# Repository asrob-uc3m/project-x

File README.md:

# project-x
Carreras de coches RC en FPV

## Materiales

### Coche
* [Coche RC - Gearbest](https://www.gearbest.com/rc-cars/pp_614987.html?wid=1433363)

### Control & FPV
* [Gafas FPV - JMT EV800 - xt-xinte](https://www.xt-xinte.com/JMT-EV800-5-Inch-800x480-Detachable-Wearing-Glasses-FPV-Goggles-40CH-Raceband-For-FPV-Racer-Quadcopter-Drone-p553991.html)
* [Cámara FPV - xt-xinte](https://www.xt-xinte.com/FPV-AIO-Micro-Camera-5-8G-25MW-40CH-800TVL-Transmitter-LST-S2-FPV-Camera-w-OSD-p497464.html)

## Otros materiales posibles
No están siendo usados por el prototipo oficial, pero sí por otros prototipos:

* [Gafas FPV - Eachine VR-007 Pro - Banggood](https://www.banggood.com/Eachine-VR-007-Pro-VR007-5_8G-40CH-HD-FPV-Goggles-4_3-Inch-Video-Headset-With-3_7V-1600mAh-Battery-p-1134154.html?rmmds=search&cur_warehouse=USA)

## Atribuciones

* [Fuente logo](https://www.dafont.com/es/dream-mma.font?text=PROJECT-X&back=theme)

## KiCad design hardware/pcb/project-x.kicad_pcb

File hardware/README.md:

Hardware
----

* GERBER - Contiene los archivos GERBER para la fabricación de la PCB
* STL - Contiene los archivos STL para la fabricación de las piezas impresas
* pcb - Contiene los archivos fuente de la PCB del coche
* backpack.fcstd - La forma de la PCB del coche en un archivo CAD (para impresión 3D y pruebas)
* cam_holder.fcstd - Pieza para sujetar la cámara FPV

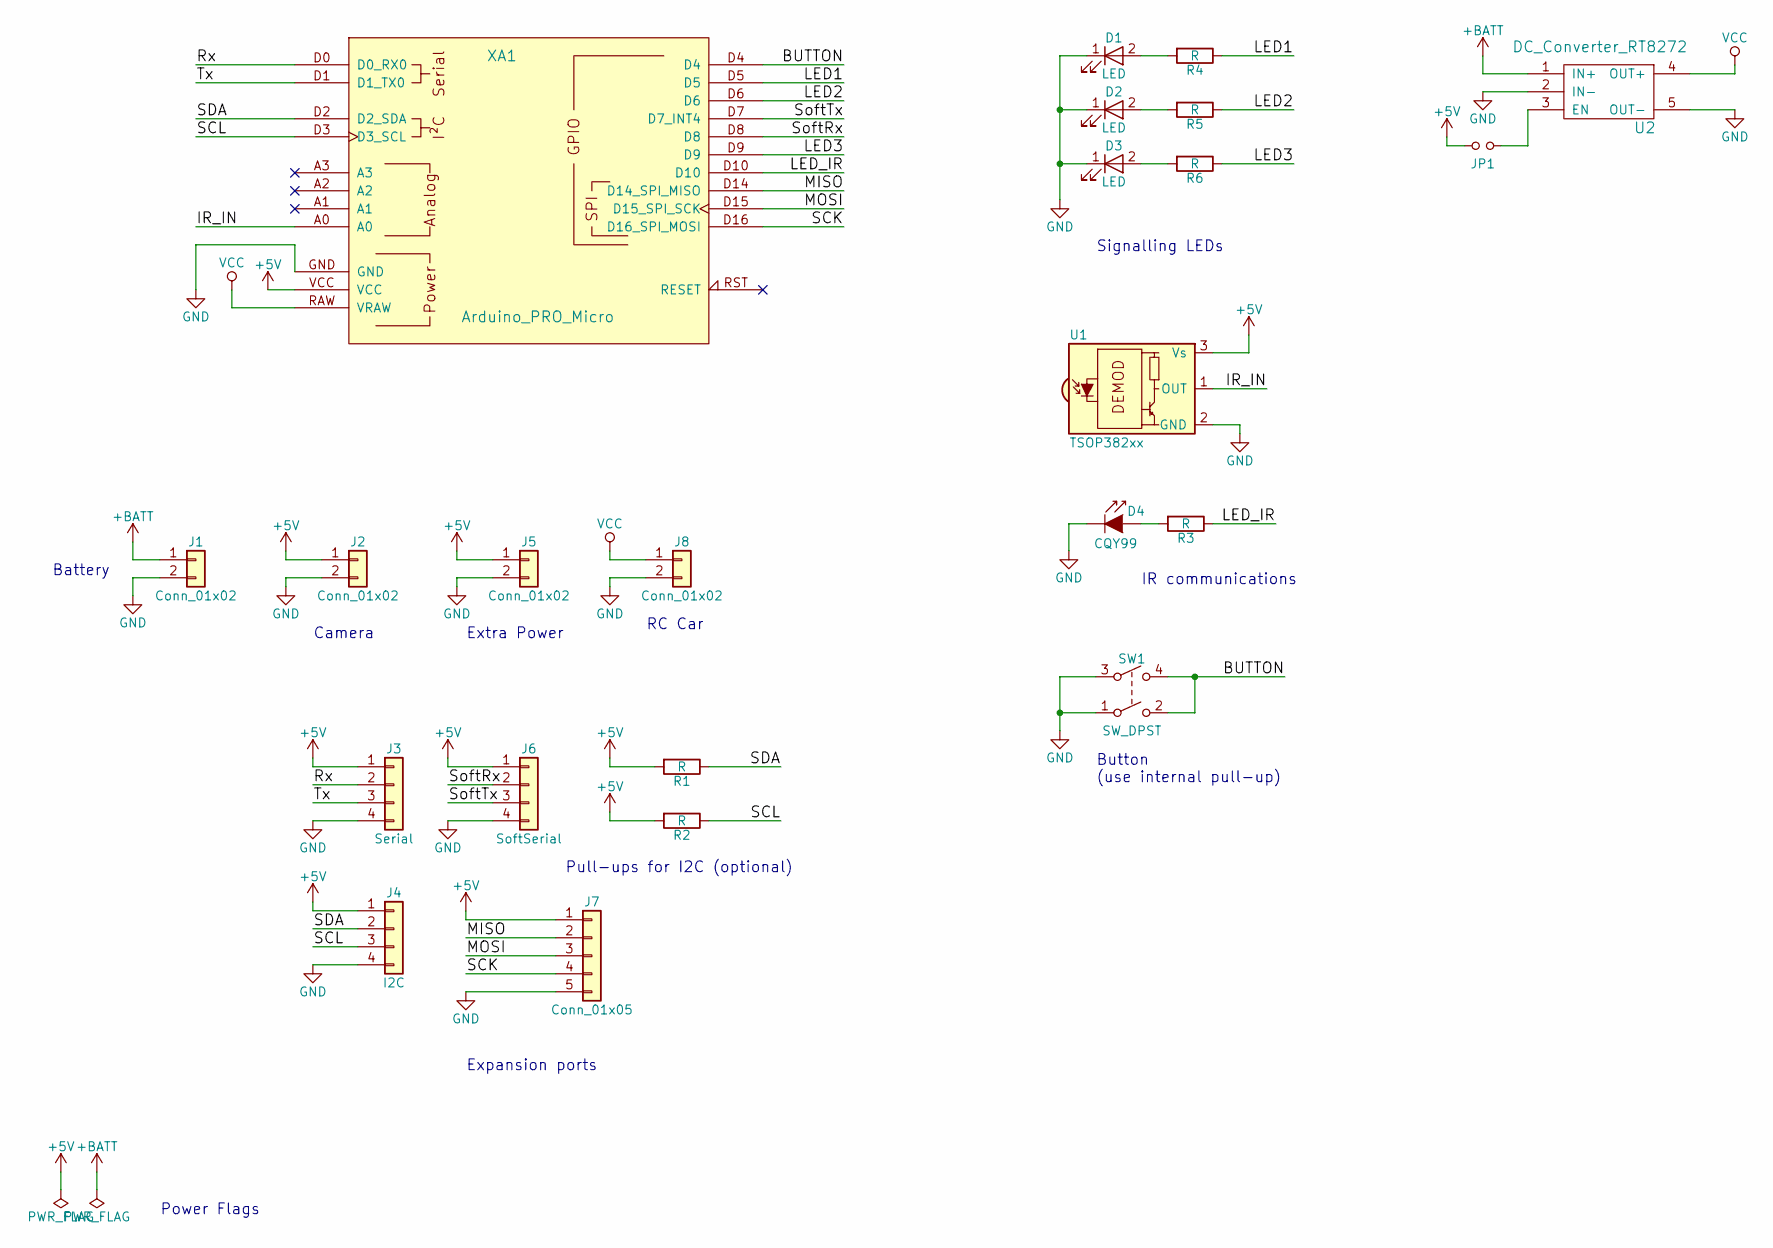
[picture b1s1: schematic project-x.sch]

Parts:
D1, D2, D3: LED; LED_0805_HandSoldering
D4: CQY99; LED_D5.0mm
J1, J2, J5, J8: Conn_01x02; Pin_Header_Straight_1x02_Pitch2.54mm
J3: Serial; Pin_Header_Straight_1x04_Pitch2.54mm
J4: I2C; Pin_Header_Straight_1x04_Pitch2.54mm
J6: SoftSerial; Pin_Header_Straight_1x04_Pitch2.54mm
J7: Conn_01x05; Pin_Header_Straight_1x05_Pitch2.54mm
JP1: Jumper_NO_Small; Miscellaneous_Solder_Jumper
R1, R2, R3, R4, R5, R6: R; R_0805_HandSoldering
SW1: SW_DPST; Switches_Push_Switch_THD
U1: TSOP382xx; IRReceiver_Vishay_MINICAST-3pin
U2: DC_Converter_RT8272; Board_DC_DC_module_RT8272
XA1: Arduino_PRO_Micro; Board_Arduino_Pro_Micro

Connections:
+5V: J2.1, J3.1, J4.1, J5.1, J6.1, J7.1, JP1.1, R1.2, R2.2, U1.3 (Vs), XA1.VCC
+BATT: J1.1, U2.1 (IN+)
/BUTTON: SW1.2, SW1.4, XA1.D4
/IR_IN: U1.1 (OUT), XA1.A0
/LED1: R4.1, XA1.D5
/LED2: R5.1, XA1.D6
/LED3: R6.1, XA1.D9
/LED_IR: R3.1, XA1.D10
/MISO: J7.2, XA1.D14 (D14_SPI_MISO)
/MOSI: J7.3, XA1.D15 (D15_SPI_SCK)
/Rx: J3.2, XA1.D0 (D0_RX0)
/SCK: J7.4, XA1.D16 (D16_SPI_MOSI)
/SCL: J4.3, R2.1, XA1.D3 (D3_SCL)
/SDA: J4.2, R1.1, XA1.D2 (D2_SDA)
/SoftRx: J6.2, XA1.D8
/SoftTx: J6.3, XA1.D7 (D7_INT4)
/Tx: J3.3, XA1.D1 (D1_TX0)
GND: D1.1 (K), D2.1 (K), D3.1 (K), D4.1 (K), J1.2, J2.2, J3.4, J4.4, J5.2, J6.4, J7.5, J8.2, SW1.1, SW1.3, U1.2 (GND), U2.2 (IN-), U2.5 (OUT-), XA1.GND
unnamed: D1.2 (A), R4.2
unnamed: D2.2 (A), R5.2
unnamed: D3.2 (A), R6.2
unnamed: D4.2 (A), R3.2
unnamed: JP1.2, U2.3 (EN)
VCC: J8.1, U2.4 (OUT+), XA1.RAW (VRAW)

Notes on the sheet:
Camera
IR communications
Battery
Signalling LEDs
Expansion ports
Pull-ups for I2C (optional)
Power Flags
Button (use internal pull-up)
RC Car
Extra Power

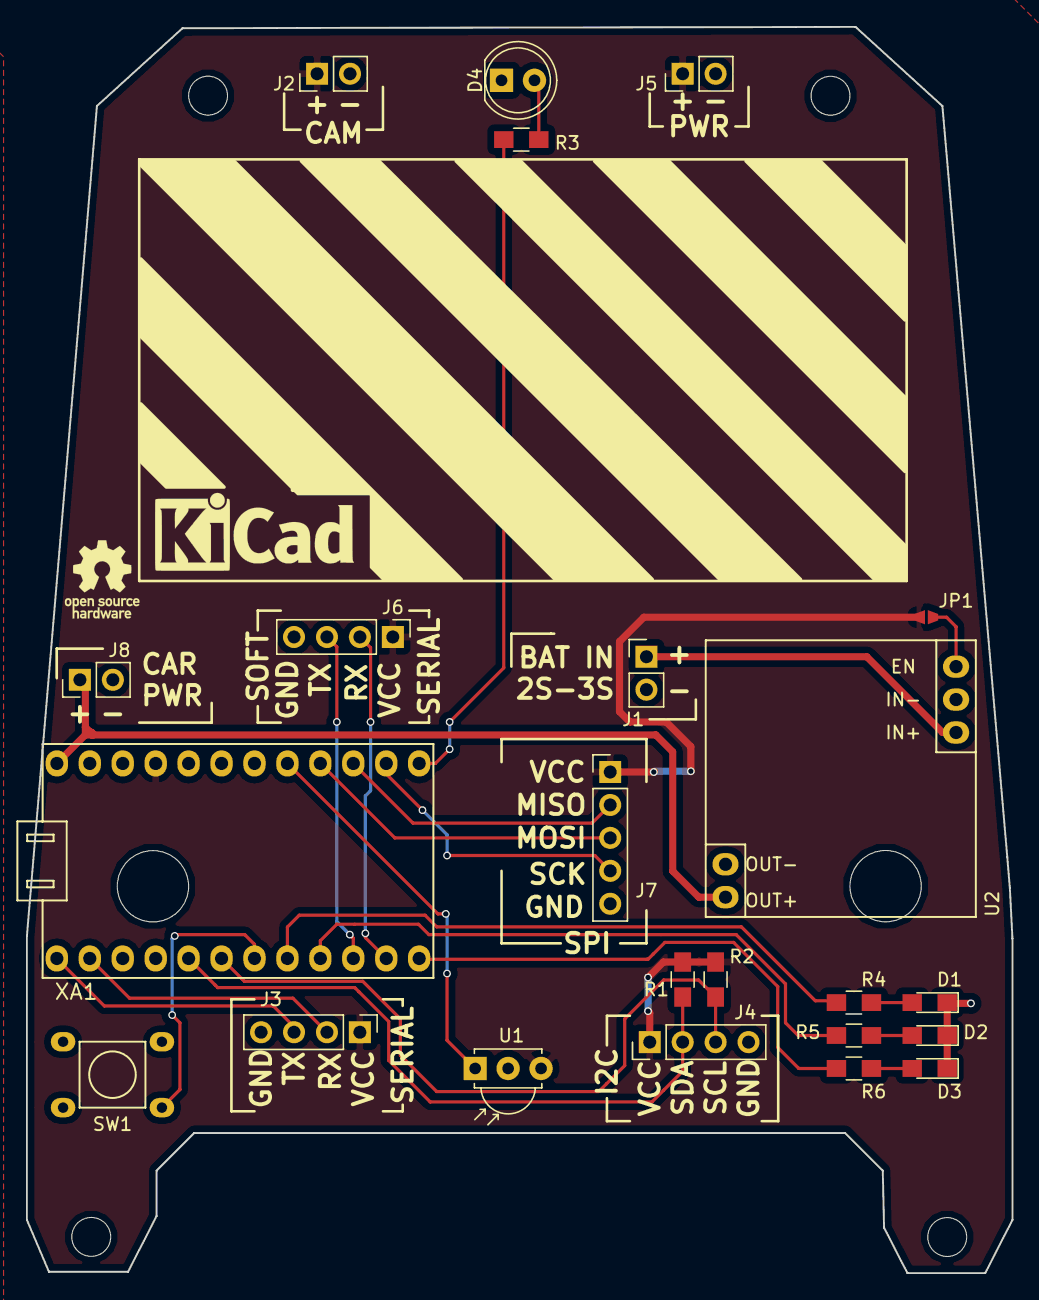
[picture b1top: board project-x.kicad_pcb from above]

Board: 2 copper layers, 76.0 x 96.1 mm, 23 parts (0 on the bottom side), 24 nets.

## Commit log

2018-10-25 Create acta-20181025
2018-10-26 Acta movida a carpeta doc
2018-10-26 Añadidas fotos de la reunión de hoy
2018-10-27 Add kicad board
2018-10-27 Add tags to schematic
2018-10-29 Add LEDs, connectors, button, IR, DC-DC
2018-10-29 Fix connections
2018-10-29 Start basic layout
2018-10-29 Add ASROB logo
2018-10-29 Add board outline as FreeCAD file
2018-10-30 Finished prototype PCB
2018-10-30 Modify backpack with correct dimensions
2018-10-30 Add author, url, version to silkcreen
2018-10-30 Modify dimensions
2018-10-30 Relocate ASROB logo
2018-11-10 Add code for driving wheel to RC controller via arduino board
2018-11-10 Add gitignore for python files
2018-11-10 Add PC code for reading driving wheel and sending to arduino
2018-11-21 Fix control from logitech driving wheel
2018-12-02 Add camera holder
2018-12-02 Upload GERBER files
2018-12-02 Move PCB to folder
2018-12-02 Add README.md
2019-01-02 Add logo
2019-03-31 Migrate controller Arduino code to ESP8266
2019-06-13 Add prototype for backpack of cheap 4x4 car
